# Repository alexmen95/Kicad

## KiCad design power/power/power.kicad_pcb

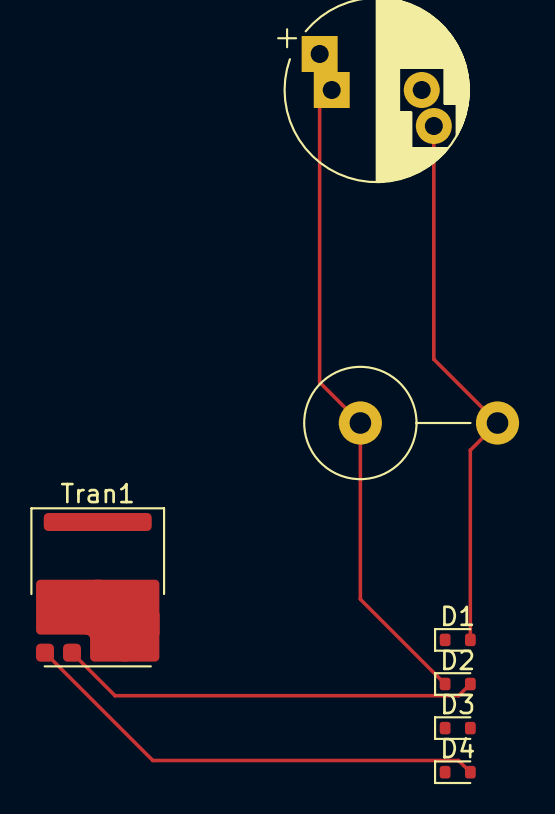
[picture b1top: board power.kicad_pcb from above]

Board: 2 copper layers, 7 parts (0 on the bottom side), 4 nets.

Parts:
C1: 500uF; CP_Radial_D10.0mm_P5.00mm_P7.50mm
D1, D2, D3, D4: 1N4148WT; D_SOD-523
R1: 500; R_Axial_DIN0617_L17.0mm_D6.0mm_P7.62mm_Vertical
Tran1: Transformer_1P_1S; GaN_Systems_GaNPX-4_7x8.4mm

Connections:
Earth: C1.2, D1.2 (A), D3.2 (A), R1.2
unnamed: D1.1 (K), D2.2 (A), Tran1.4 (SB)
unnamed: C1.1, D2.1 (K), D4.1 (K), R1.1
unnamed: D3.1 (K), D4.2 (A), Tran1.3 (SA)

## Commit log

2024-09-03 Files and directrories added for tracking
